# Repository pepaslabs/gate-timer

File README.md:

# gate-timer

A beam-interrupt timer with a large 7-segment display.

# UNTESTED

This board design is untested.

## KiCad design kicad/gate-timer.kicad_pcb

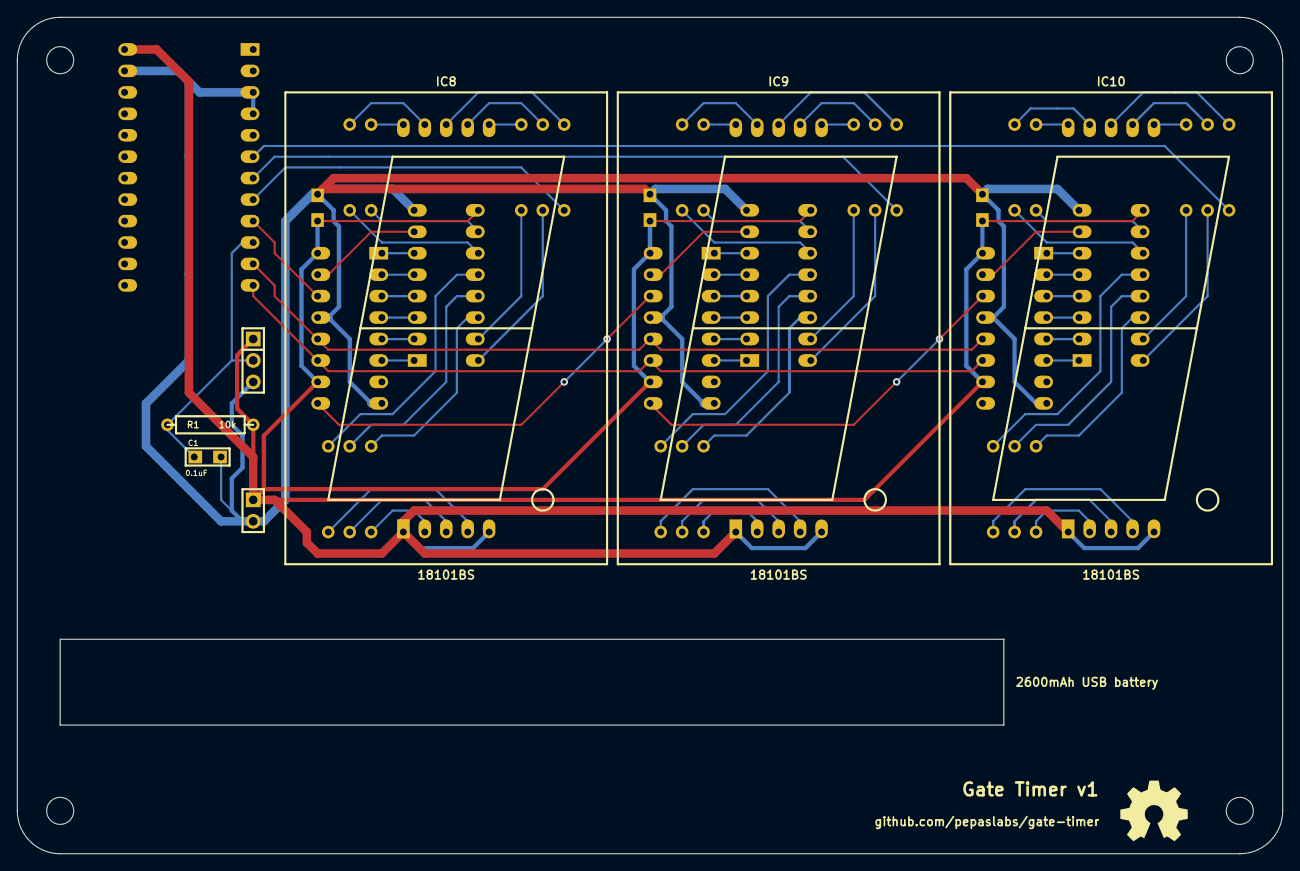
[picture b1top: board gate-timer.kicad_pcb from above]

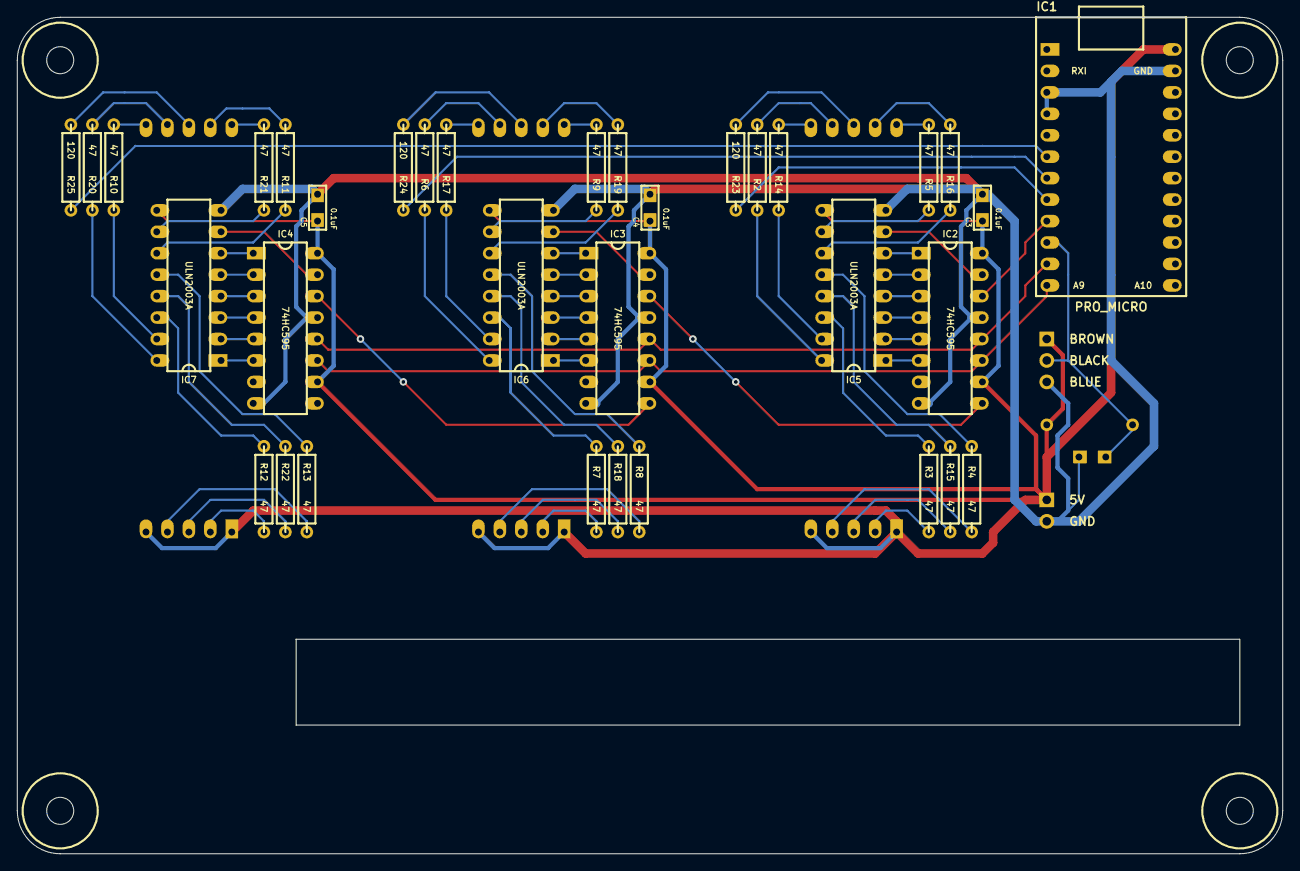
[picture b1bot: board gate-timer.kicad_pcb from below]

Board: 2 copper layers, 149.9 x 99.1 mm, 55 parts (38 on the bottom side), 77 nets.

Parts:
C1, C3, C4, C5: 0.1uF; PL_CERCAP_15_059B_0805
H***: Val**; PL_hole_25_1
H***#2, H***#3, H***#4, H***#5, H***#6, H***#11, H***#12, H***#13, H***#14: Val**; PL_hole_25_1
H***#7, H***#8, H***#9, H***#10: Val**; PL_hole_M3_NPTH
IC1: PRO_MICRO; PL_PRO_MICRO
IC2, IC3, IC4: 74HC595; PL_DIP16
IC5, IC6, IC7: ULN2003A; PL_DIP16
IC8, IC9, IC10: 18101BS; PL_18101BS
P1: CONN_3X1; PL_SIL-3
P2: CONN_2X1; PL_SIL-2
R1: 10k; PL_R_AXIAL_0W25_059A
R2, R3, R4, R5, R6, R7, R8, R9, R10, R11, R12, R13, R14, R15, R16, R17, R18, R19, R20, R21, R22: 47; PL_R_AXIAL_0W25_059A
R23, R24, R25: 120; PL_R_AXIAL_0W25_059A

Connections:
5V: C3.1, C4.1, C5.1, IC1.24, IC2.10, IC2.16, IC3.10, IC3.16, IC4.10, IC4.16, IC5.9, IC6.9, IC7.9, IC8.1, IC8.5, IC9.1, IC9.5, IC10.1, IC10.5, P1.1, P2.1, R1.2
CLOCK: IC1.12, IC2.11, IC3.11, IC4.11
DATA: IC1.9, IC2.14
DP1: IC1.8, R23.1
DP2: IC1.7, R24.1
DP3: IC1.6, R25.1
GND: C1.2, C3.2, C4.2, C5.2, IC1.3, IC1.4, IC1.23, IC2.8, IC2.13, IC3.8, IC3.13, IC4.8, IC4.13, IC5.8, IC6.8, IC7.8, P1.3, P2.2
LATCH: IC1.11, IC2.12, IC3.12, IC4.12
unnamed: IC4.15, IC7.7
unnamed: IC10.8, R25.2
unnamed: IC4.6, IC7.1
unnamed: IC3.9, IC4.14
unnamed: IC2.9, IC3.14
unnamed: IC7.11, R11.1
unnamed: IC7.14, R12.1
unnamed: IC10.2, R12.2
unnamed: IC7.12, R13.1
unnamed: IC10.4, R13.2
unnamed: IC7.16, R20.1
unnamed: IC10.7, R20.2
unnamed: IC7.10, R21.1
unnamed: IC7.15, R10.1
unnamed: IC10.10, R21.2
unnamed: IC10.9, R11.2
unnamed: IC10.6, R10.2
unnamed: IC4.1, IC7.6
unnamed: IC4.2, IC7.5
unnamed: IC4.3, IC7.4
unnamed: IC4.4, IC7.3
unnamed: IC4.5, IC7.2
unnamed: IC7.13, R22.1
unnamed: IC8.4, R4.2
unnamed: IC8.7, R2.2
unnamed: IC8.6, R14.2
unnamed: IC8.3, R15.2
unnamed: IC10.3, R22.2
unnamed: IC9.10, R9.2
unnamed: IC8.2, R3.2
unnamed: IC8.10, R5.2
unnamed: IC5.14, R3.1
unnamed: IC5.12, R4.1
unnamed: IC5.10, R5.1
unnamed: IC5.11, R16.1
unnamed: IC5.13, R15.1
unnamed: IC5.15, R14.1
unnamed: IC5.16, R2.1
unnamed: IC8.9, R16.2
unnamed: IC2.15, IC5.7
unnamed: IC2.3, IC5.4
unnamed: IC2.4, IC5.3
unnamed: IC2.5, IC5.2
unnamed: IC2.6, IC5.1
unnamed: IC2.2, IC5.5
unnamed: IC2.1, IC5.6
unnamed: IC8.8, R23.2
unnamed: IC3.2, IC6.5
unnamed: IC9.3, R18.2
unnamed: IC9.4, R8.2
unnamed: IC3.1, IC6.6
unnamed: IC3.3, IC6.4
unnamed: IC3.4, IC6.3
unnamed: IC3.5, IC6.2
unnamed: IC3.6, IC6.1
unnamed: IC9.2, R7.2
unnamed: IC9.6, R17.2
unnamed: IC9.7, R6.2
unnamed: IC9.9, R19.2
unnamed: IC6.15, R17.1
unnamed: IC9.8, R24.2
unnamed: IC3.15, IC6.7
unnamed: IC6.14, R7.1
unnamed: IC6.16, R6.1
unnamed: IC6.11, R19.1
unnamed: IC6.12, R8.1
unnamed: IC6.10, R9.1
unnamed: IC6.13, R18.1
TRIGGER: C1.1, IC1.10, P1.2, R1.1

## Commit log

2022-07-02 Initial import
2022-07-09 v1 schematic
2022-07-09 initial firmware implementation
2022-07-09 scrolling marquee for final time
2022-07-10 base 60 display mode (seconds, minutes, hours, etc)
